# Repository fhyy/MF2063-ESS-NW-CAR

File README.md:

clear
To access the flag on your phone or computer, go to [this site.](https://fhyy.github.io/MF2063-ESS-NW-CAR/index.html)  
If you have an Android phone, you could instead install the program from the [MF2063-ESS-NW-CAR-AndroidApp](https://github.com/fhyy/MF2063-ESS-NW-CAR-AndroidApp) repository.

# Introduction
**Network diagram**  

# Instructions
_TODO_

# Contributing

## Coding conventions

The project follows a set of coding guidelines to keep the code consistent between the files. The guidelines have been adopted from the Mono project and can be found [here](https://github.com/mono/website/blob/gh-pages/community/contributing/coding-guidelines.md) ([alternative link](https://www.mono-project.com/community/contributing/coding-guidelines/)). Note that thesse guidelines have been developed for C# and some adaption may need to happen to fit the different langauges we use. Summaries of the most important parts follow below as well as a cheat sheet.

### Indentation

Use tabs for indentation. Set your text-editor to show them as 8 spaces to incentivise little nesting of loops.

### Where to put braces

| Statement                   | Brace position |
|-----------------------------|----------------|
| Namespace                   | same line      |
| Type                        | same line      |
| Method (including ctor)     | **new line**       |
| Properties                  | same line      |
| Control blocks (if, for...) | same line      |
| Anonymous types and methods | same line      |

### File headers

File headers should inlude file name and a short description of the file as well as the authors of the files. Feel free to use the following template.

```
//
// control.c: Contains the control system functionality.
//
// Authors:
//      John Doe (johndoe@address.com)
//
// License:
//      AFL 3.0 
//
```

### Important sections/cheat sheet

- [Indentation](https://www.mono-project.com/community/contributing/coding-guidelines/#indentation)
- [Where to put spaces](https://www.mono-project.com/community/contributing/coding-guidelines/#where-to-put-spaces)
- [Where to put braces](https://www.mono-project.com/community/contributing/coding-guidelines/#where-to-put-braces)
- [Multiline parameter](https://www.mono-project.com/community/contributing/coding-guidelines/#multiline-parameters)
- [Whitespace for clarity](https://www.mono-project.com/community/contributing/coding-guidelines/#use-whitespace-for-clarity)
- [Multiline comments](https://www.mono-project.com/community/contributing/coding-guidelines/#multiline-comments)
- [Casing](https://www.mono-project.com/community/contributing/coding-guidelines/#casing)

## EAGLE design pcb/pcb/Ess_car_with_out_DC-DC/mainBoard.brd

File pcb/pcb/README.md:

# PCBs

# Board for Arduino IR esc
This is the file for the Arduino board to connect the the Speed sensor and ESC to steer them from Arduino 

# Board for Arduino ultras servo 
This is the file for the Arduino board to connect Ultrasound and steering servo.

# Ess car 
Is the file for the power unit and includes the boost converter 

# Ess car with out DC-DC
This the design for the power unit with out the boost converter.

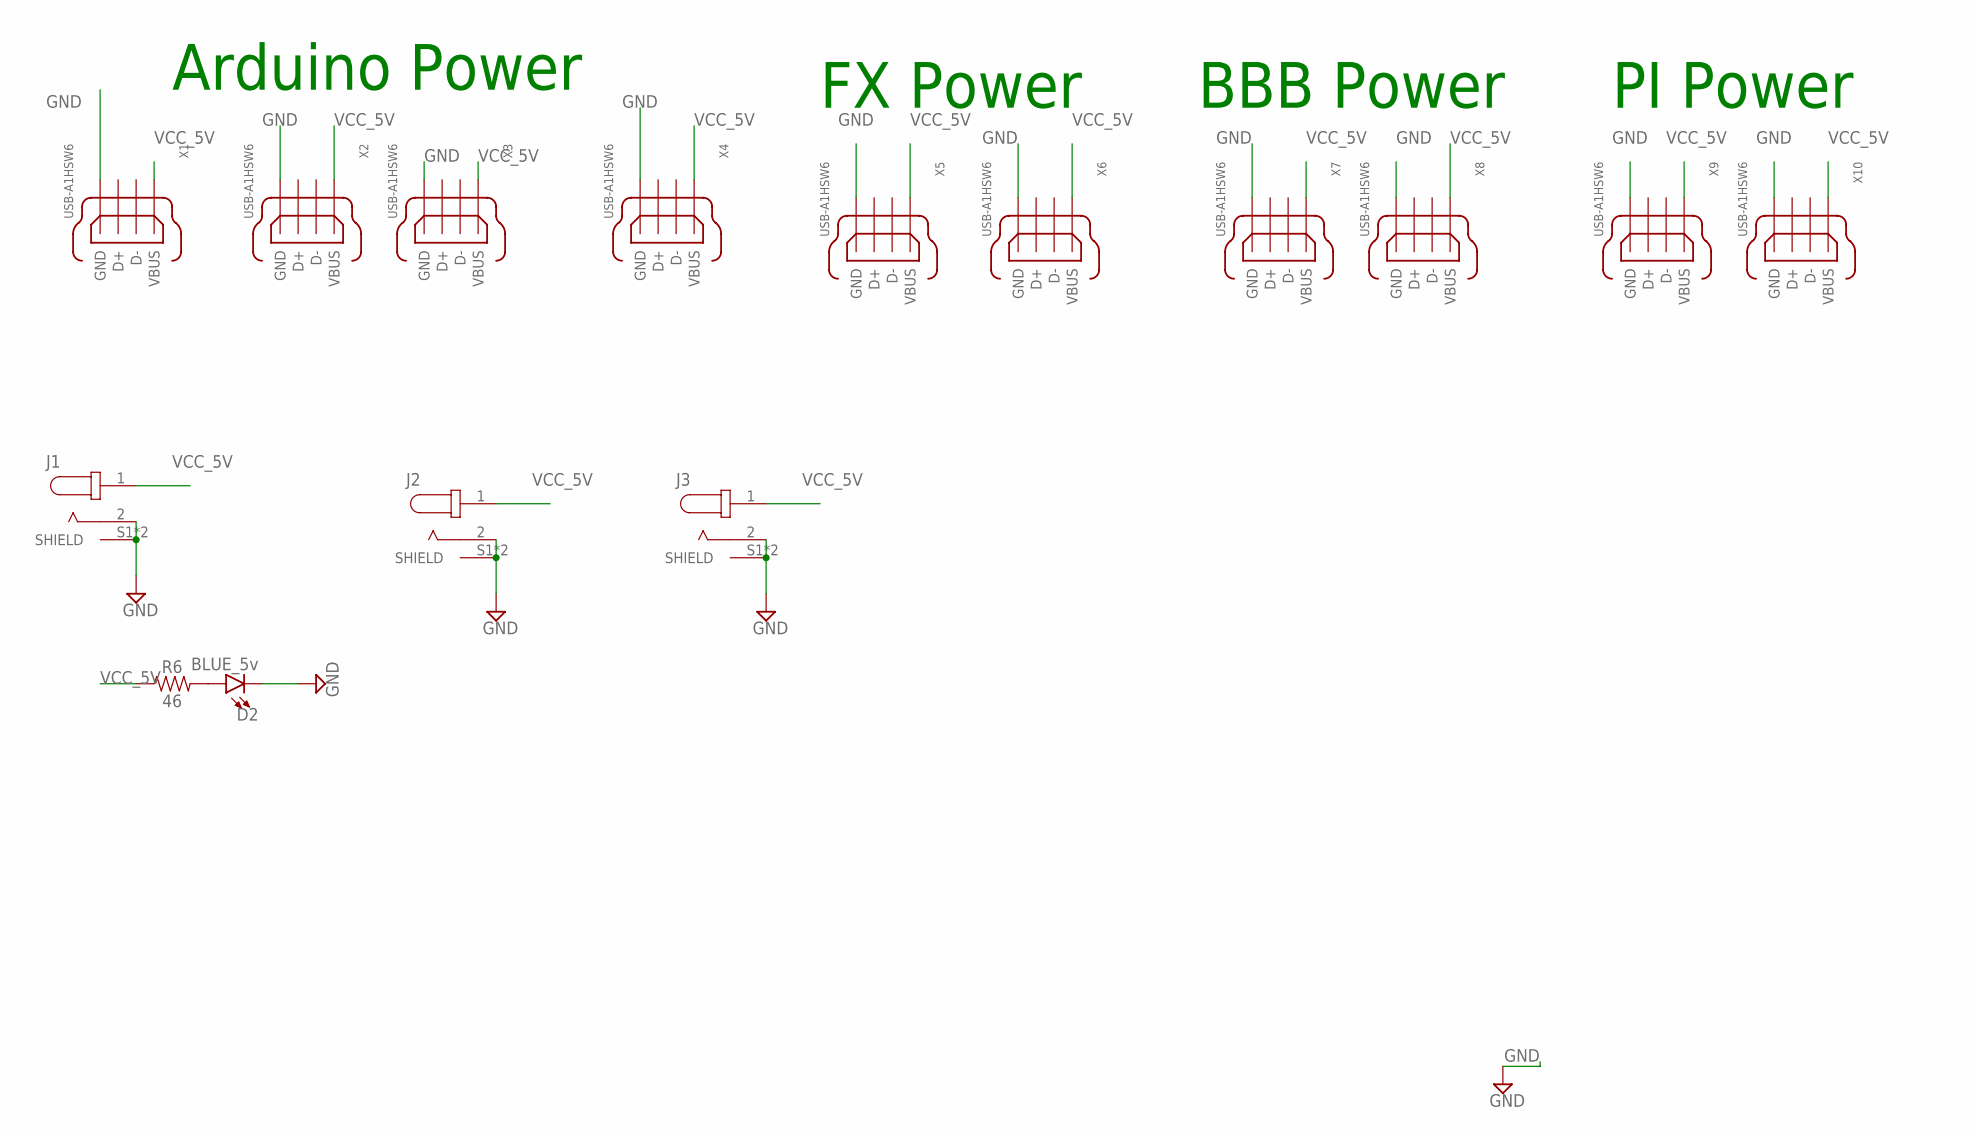
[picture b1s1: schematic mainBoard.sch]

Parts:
D2: BLUE_5v; LED-0603
J1, J2, J3: PJ-063AH; CUI_PJ-063AH
R6: 46; 0603
X1, X2, X3, X4, X5, X6, X7, X8, X9, X10: USB-A1HSW6; OST_USB-A1HSW6

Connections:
GND: D2.C, J1.2, J1.S1 (SHIELD), J1.S2 (SHIELD), J2.2, J2.S1 (SHIELD), J2.S2 (SHIELD), J3.2, J3.S1 (SHIELD), J3.S2 (SHIELD), X1.4 (GND), X2.4 (GND), X3.4 (GND), X4.4 (GND), X5.4 (GND), X6.4 (GND), X7.4 (GND), X8.4 (GND), X9.4 (GND), X10.4 (GND)
unnamed: D2.A, R6.2
VCC_5V: J1.1, J2.1, J3.1, R6.1, X1.1 (VBUS), X2.1 (VBUS), X3.1 (VBUS), X4.1 (VBUS), X5.1 (VBUS), X6.1 (VBUS), X7.1 (VBUS), X8.1 (VBUS), X9.1 (VBUS), X10.1 (VBUS)

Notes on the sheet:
Arduino Power
FX Power
BBB Power
PI Power

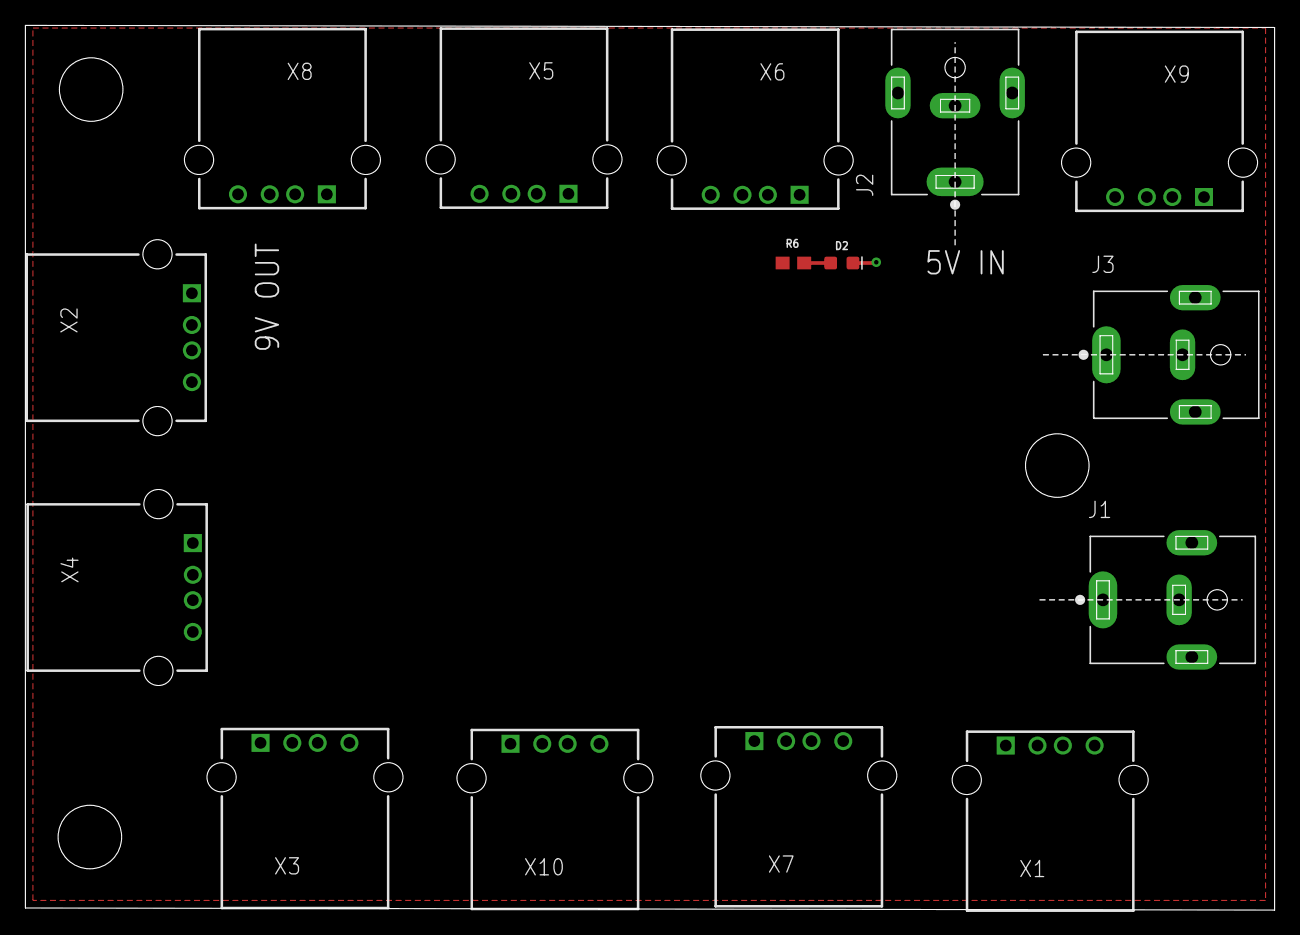
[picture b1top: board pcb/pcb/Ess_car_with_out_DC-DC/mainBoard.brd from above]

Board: 2 copper layers, 98.4 x 69.7 mm, 15 parts (0 on the bottom side), 3 nets.

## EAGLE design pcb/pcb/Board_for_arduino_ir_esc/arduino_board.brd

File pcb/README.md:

# PCB and schematics for the powering and communication 
In the "Power schematics" is the simulation file for the boost converter. The simulation program is MPLAB from Microchip and is used because the an IC from Microchip. In the folder pcb is the Eagle files for the power unit and the Arduino boards.

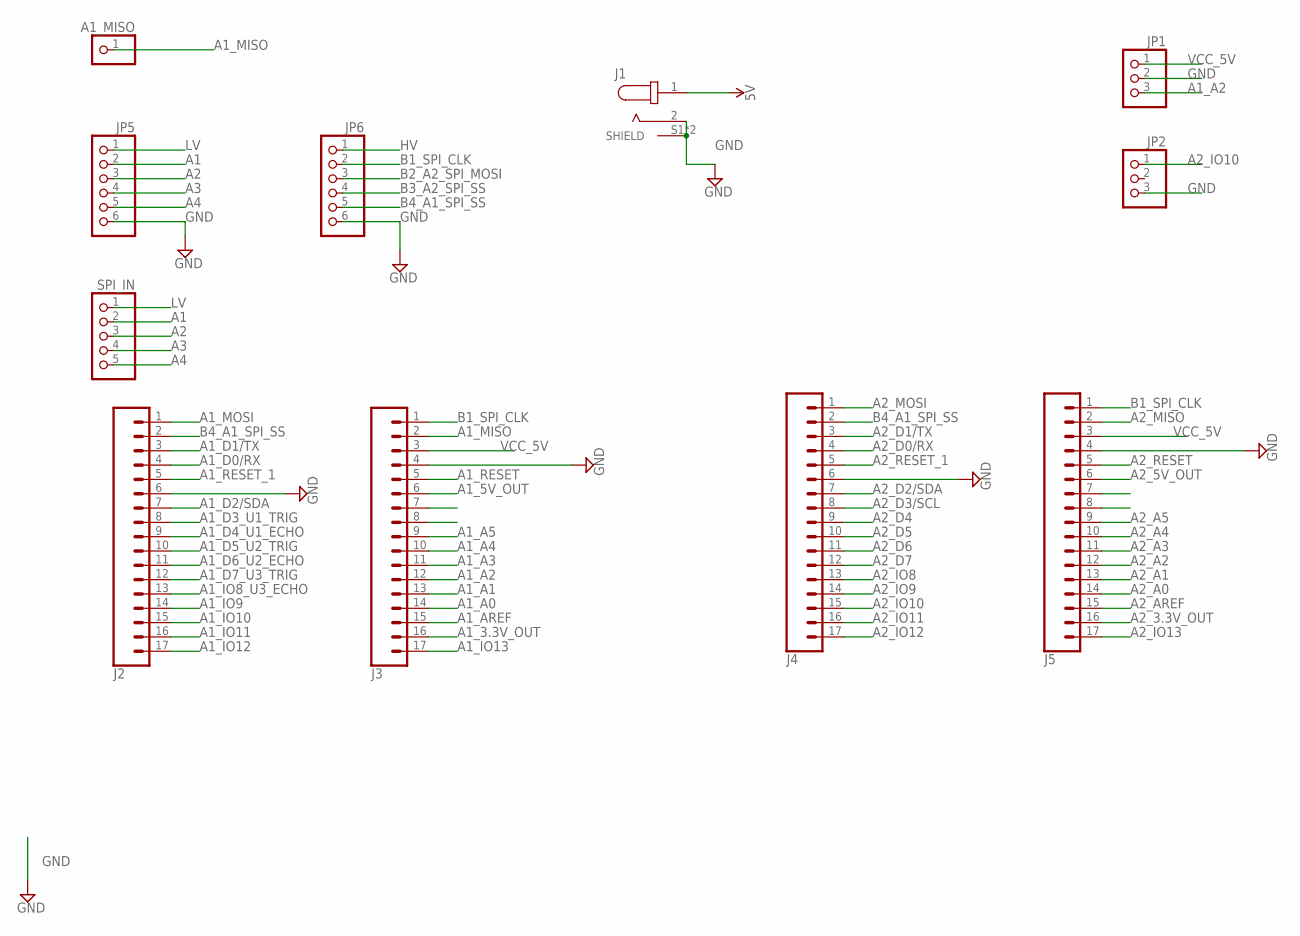
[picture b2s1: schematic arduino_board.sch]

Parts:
A1_MISO: PINHD-1X1; 1X01
J1: PJ-063AH; CUI_PJ-063AH
J2, J3, J4, J5: CONN_17; 1X17
JP1, JP2: PINHD-1X3; 1X03
JP5, JP6: PINHD-1X6; 1X06
SPI_IN: PINHD-1X5; 1X05

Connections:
5V: J1.1
A1: JP5.2, SPI_IN.2
A1_3.3V_OUT: J3.16
A1_5V_OUT: J3.6
A1_A0: J3.14
A1_A1: J3.13
A1_A2: J3.12, JP1.3
A1_A3: J3.11
A1_A4: J3.10
A1_A5: J3.9
A1_AREF: J3.15
A1_D0/RX: J2.4
A1_D1/TX: J2.3
A1_D2/SDA: J2.7
A1_D3_U1_TRIG: J2.8
A1_D4_U1_ECHO: J2.9
A1_D5_U2_TRIG: J2.10
A1_D6_U2_ECHO: J2.11
A1_D7_U3_TRIG: J2.12
A1_IO8_U3_ECHO: J2.13
A1_IO9: J2.14
A1_IO10: J2.15
A1_IO11: J2.16
A1_IO12: J2.17
A1_IO13: J3.17
A1_MISO: A1_MISO.1, J3.2
A1_MOSI: J2.1
A1_RESET: J3.5
A1_RESET_1: J2.5
A2: JP5.3, SPI_IN.3
A2_3.3V_OUT: J5.16
A2_5V_OUT: J5.6
A2_A0: J5.14
A2_A1: J5.13
A2_A2: J5.12
A2_A3: J5.11
A2_A4: J5.10
A2_A5: J5.9
A2_AREF: J5.15
A2_D0/RX: J4.4
A2_D1/TX: J4.3
A2_D2/SDA: J4.7
A2_D3/SCL: J4.8
A2_D4: J4.9
A2_D5: J4.10
A2_D6: J4.11
A2_D7: J4.12
A2_IO8: J4.13
A2_IO9: J4.14
A2_IO10: J4.15, JP2.1
A2_IO11: J4.16
A2_IO12: J4.17
A2_IO13: J5.17
A2_MISO: J5.2
A2_MOSI: J4.1
A2_RESET: J5.5
A2_RESET_1: J4.5
A3: JP5.4, SPI_IN.4
A4: JP5.5, SPI_IN.5
B1_SPI_CLK: J3.1, J5.1, JP6.2
B2_A2_SPI_MOSI: JP6.3
B3_A2_SPI_SS: JP6.4
B4_A1_SPI_SS: J2.2, J4.2, JP6.5
GND: J1.2, J1.S1 (SHIELD), J1.S2 (SHIELD), J2.6, J3.4, J4.6, J5.4, JP1.2, JP2.3, JP5.6, JP6.6
HV: JP6.1
LV: JP5.1, SPI_IN.1
VCC_5V: J3.3, J5.3, JP1.1

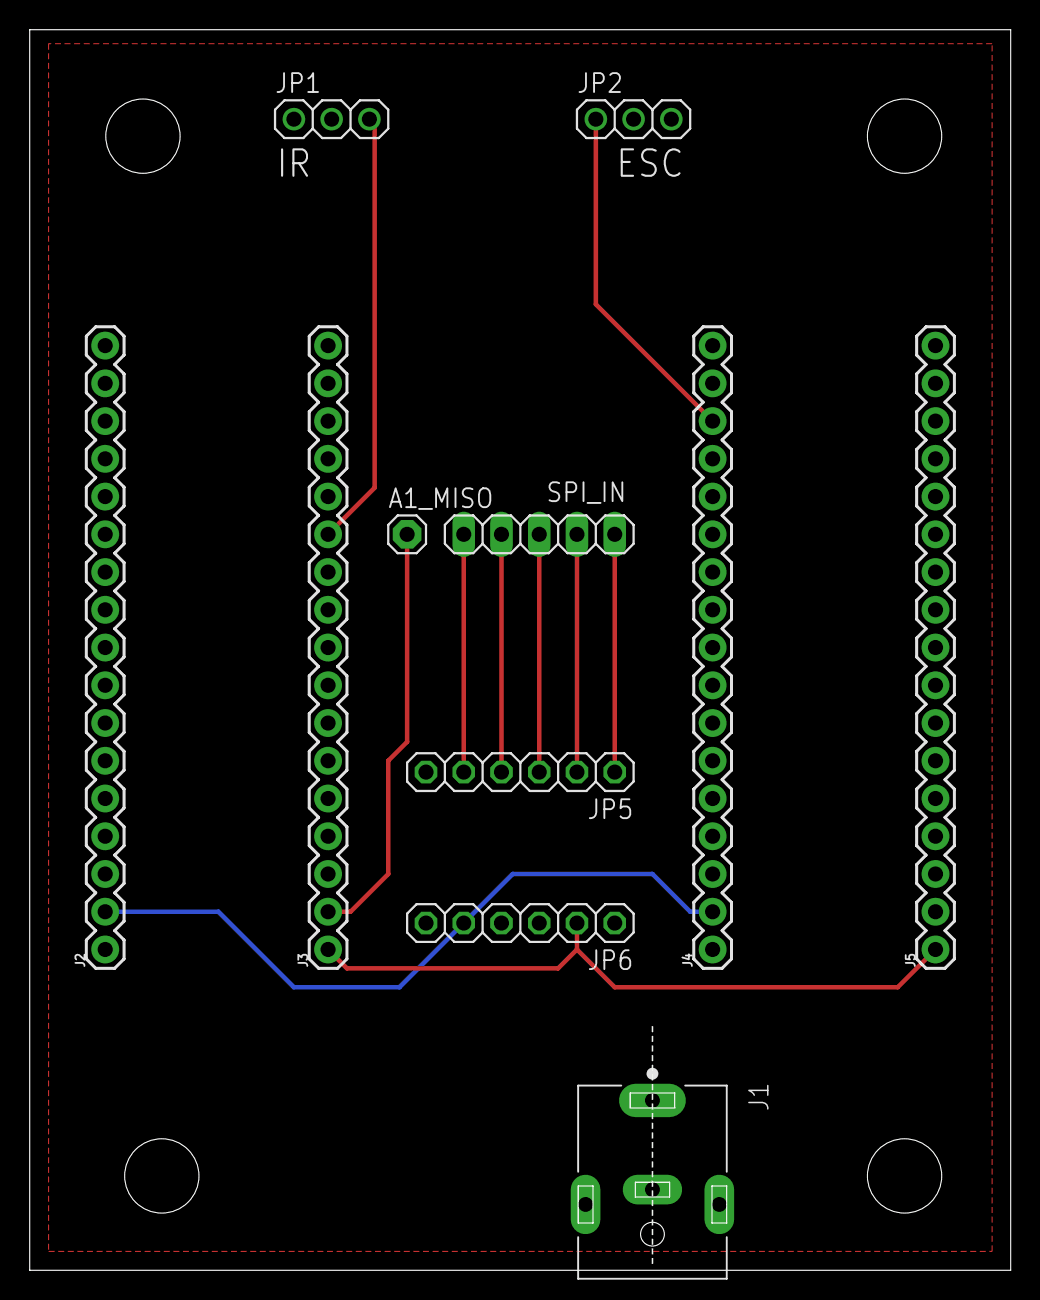
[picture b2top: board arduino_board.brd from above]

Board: 2 copper layers, 66.0 x 83.5 mm, 11 parts (0 on the bottom side), 12 nets.

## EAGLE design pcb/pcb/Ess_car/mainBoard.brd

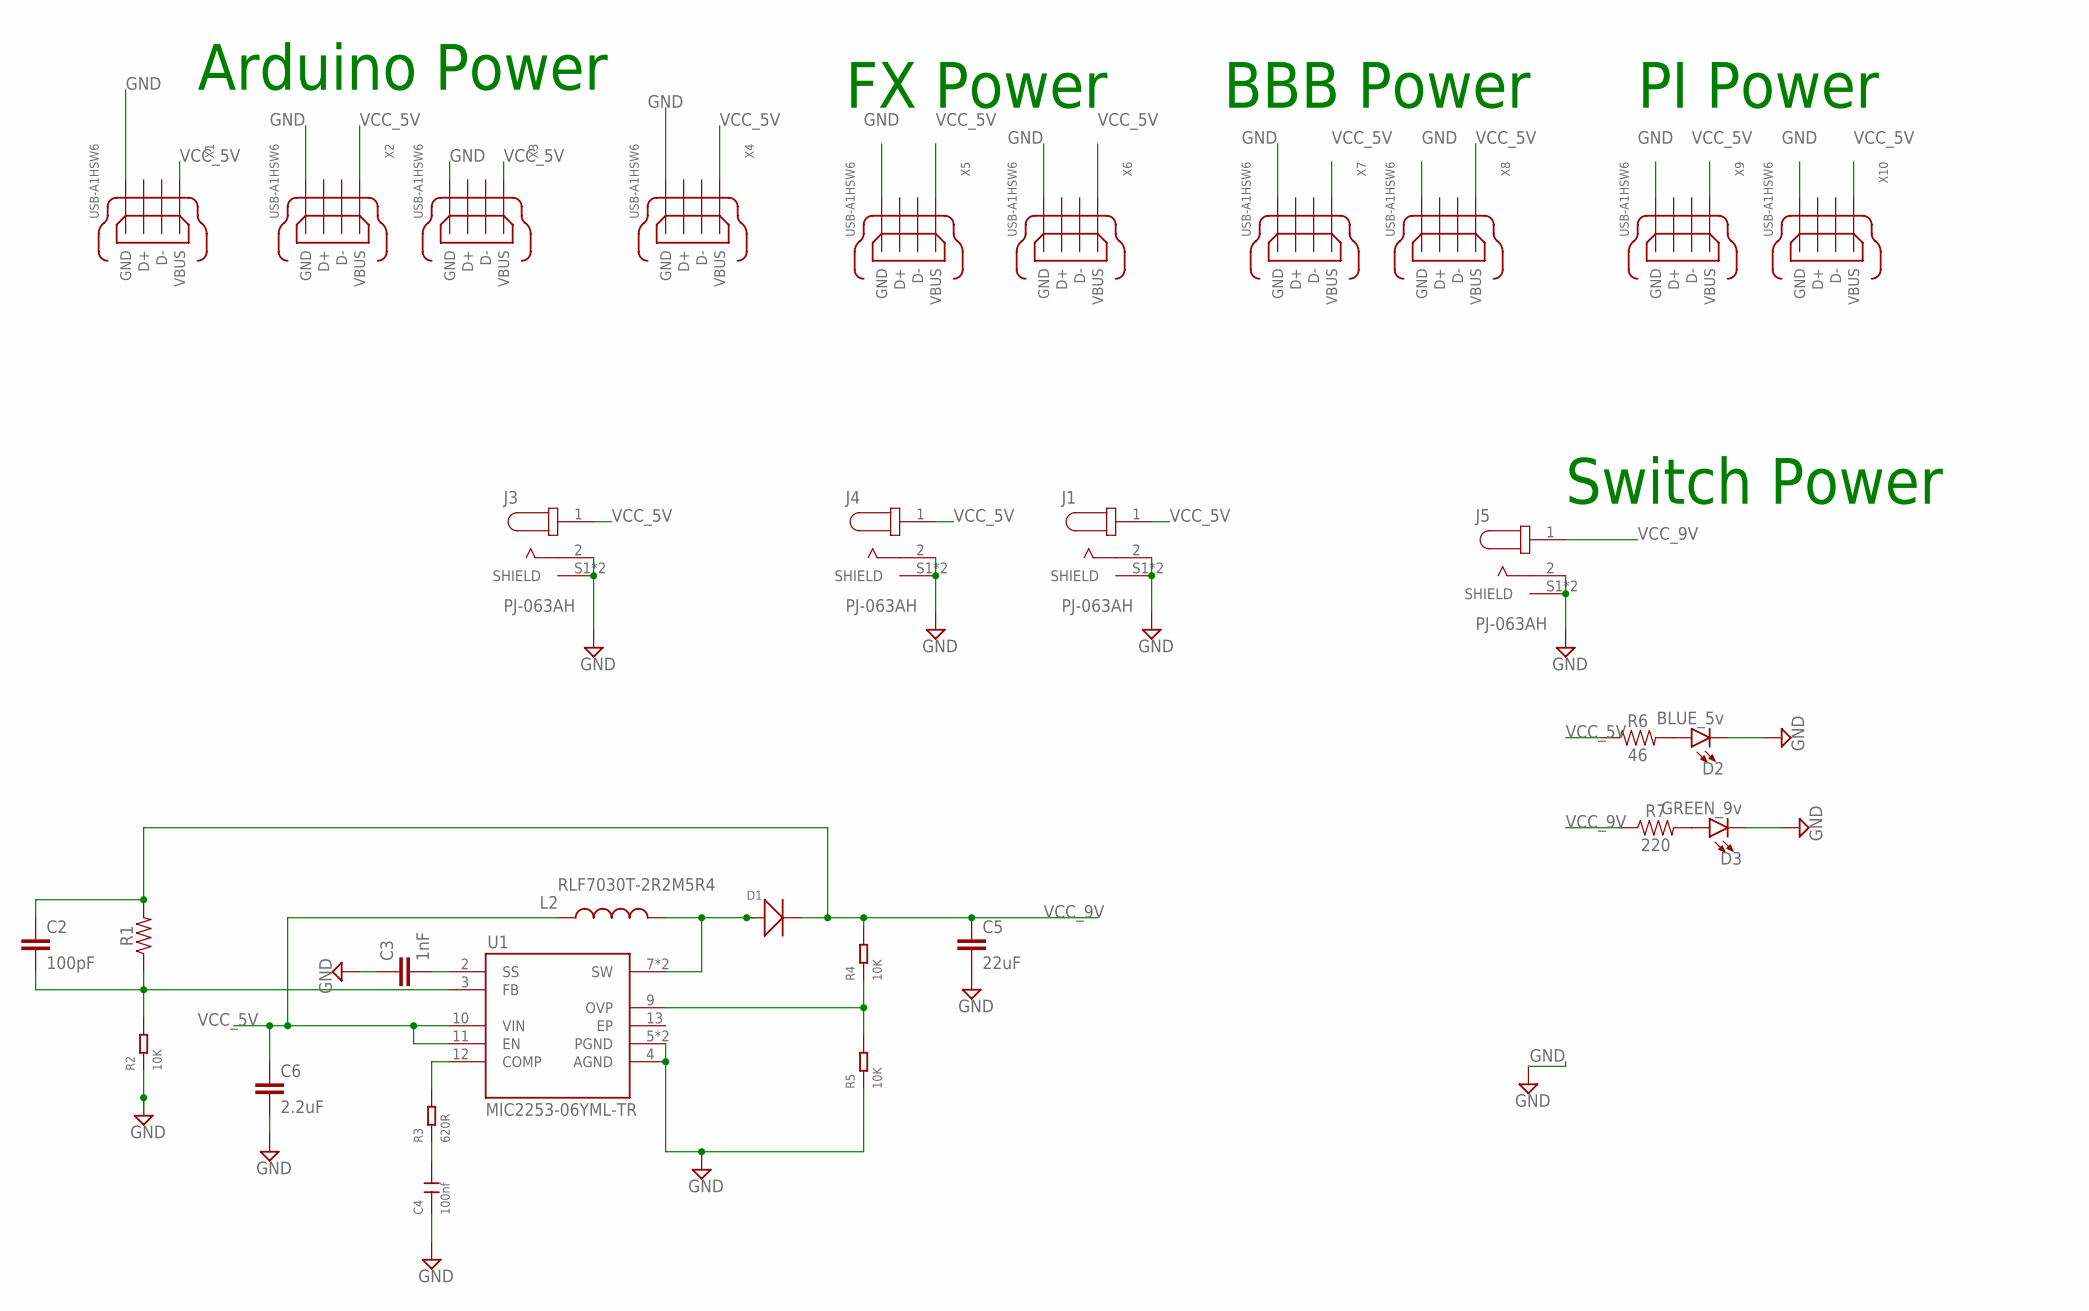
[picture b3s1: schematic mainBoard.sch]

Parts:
C2: 100pF; 0603
C3: 1nF; 0603
C4: 100nf; C0402
C5: 22uF; 0805
C6: 2.2uF; 0603
D1: SMD-DIODE-SCHOTTKY-28V-5A(DO-214AA); DO-214AA
D2: BLUE_5v; LED-0603
D3: GREEN_9v; LED-0603
J1, J3, J4, J5: PJ-063AH; CUI_PJ-063AH
L2: RLF7030T-2R2M5R4; INDP7368X320
R1: 62KOHM-0603-1/10W-5%; 0603
R2, R4, R5: 10K; R0603
R3: 620R; R0603
R6: 46; 0603
R7: 220; 0603
U1: MIC2253-06YML-TR; SON50P300X300X90-13N
X1, X2, X3, X4, X5, X6, X7, X8, X9, X10: USB-A1HSW6; OST_USB-A1HSW6

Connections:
GND: C3.1, C4.1, C5.2, C6.2, D2.C, D3.C, J1.2, J1.S1 (SHIELD), J1.S2 (SHIELD), J3.2, J3.S1 (SHIELD), J3.S2 (SHIELD), J4.2, J4.S1 (SHIELD), J4.S2 (SHIELD), J5.2, J5.S1 (SHIELD), J5.S2 (SHIELD), R2.1, R5.1, U1.4 (AGND), U1.5 (PGND), U1.6 (PGND), X1.4 (GND), X2.4 (GND), X3.4 (GND), X4.4 (GND), X5.4 (GND), X6.4 (GND), X7.4 (GND), X8.4 (GND), X9.4 (GND), X10.4 (GND)
unnamed: C3.2, U1.2 (SS)
unnamed: D2.A, R6.2
unnamed: R3.2, U1.12 (COMP)
unnamed: C4.2, R3.1
unnamed: C2.2, R1.1, R2.2, U1.3 (FB)
unnamed: R4.1, R5.2, U1.9 (OVP)
unnamed: D3.A, R7.2
unnamed: D1.+, L2.2, U1.7 (SW), U1.8 (SW)
VCC_5V: C6.1, J1.1, J3.1, J4.1, L2.1, R6.1, U1.10 (VIN), U1.11 (EN), X1.1 (VBUS), X2.1 (VBUS), X3.1 (VBUS), X4.1 (VBUS), X5.1 (VBUS), X6.1 (VBUS), X7.1 (VBUS), X8.1 (VBUS), X9.1 (VBUS), X10.1 (VBUS)
VCC_9V: C2.1, C5.1, D1.-, J5.1, R1.2, R4.2, R7.1

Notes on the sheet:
Arduino Power
FX Power
BBB Power
PI Power
Switch Power

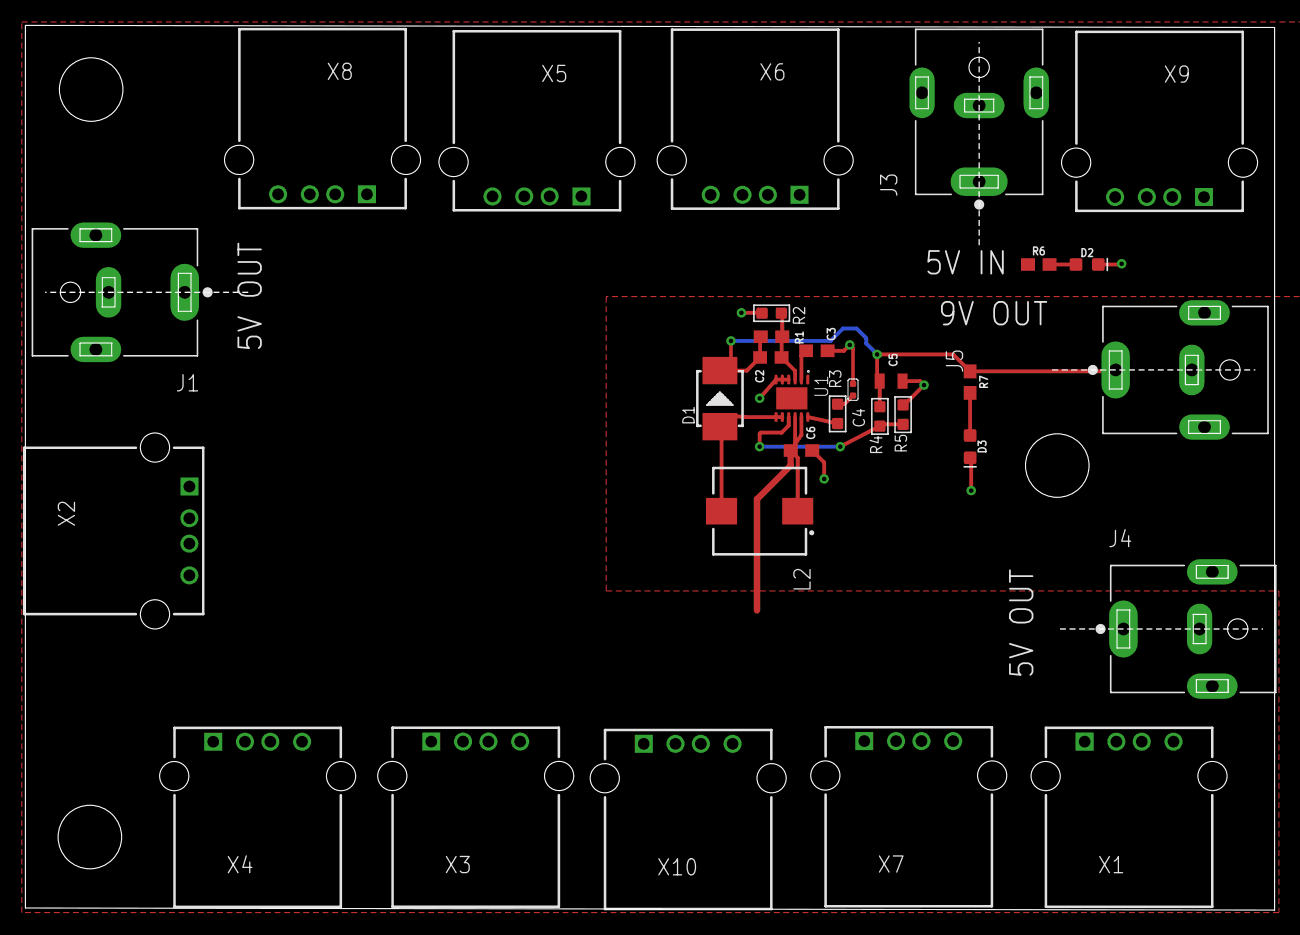
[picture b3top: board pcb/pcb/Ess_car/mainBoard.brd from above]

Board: 2 copper layers, 98.4 x 69.7 mm, 31 parts (0 on the bottom side), 11 nets.

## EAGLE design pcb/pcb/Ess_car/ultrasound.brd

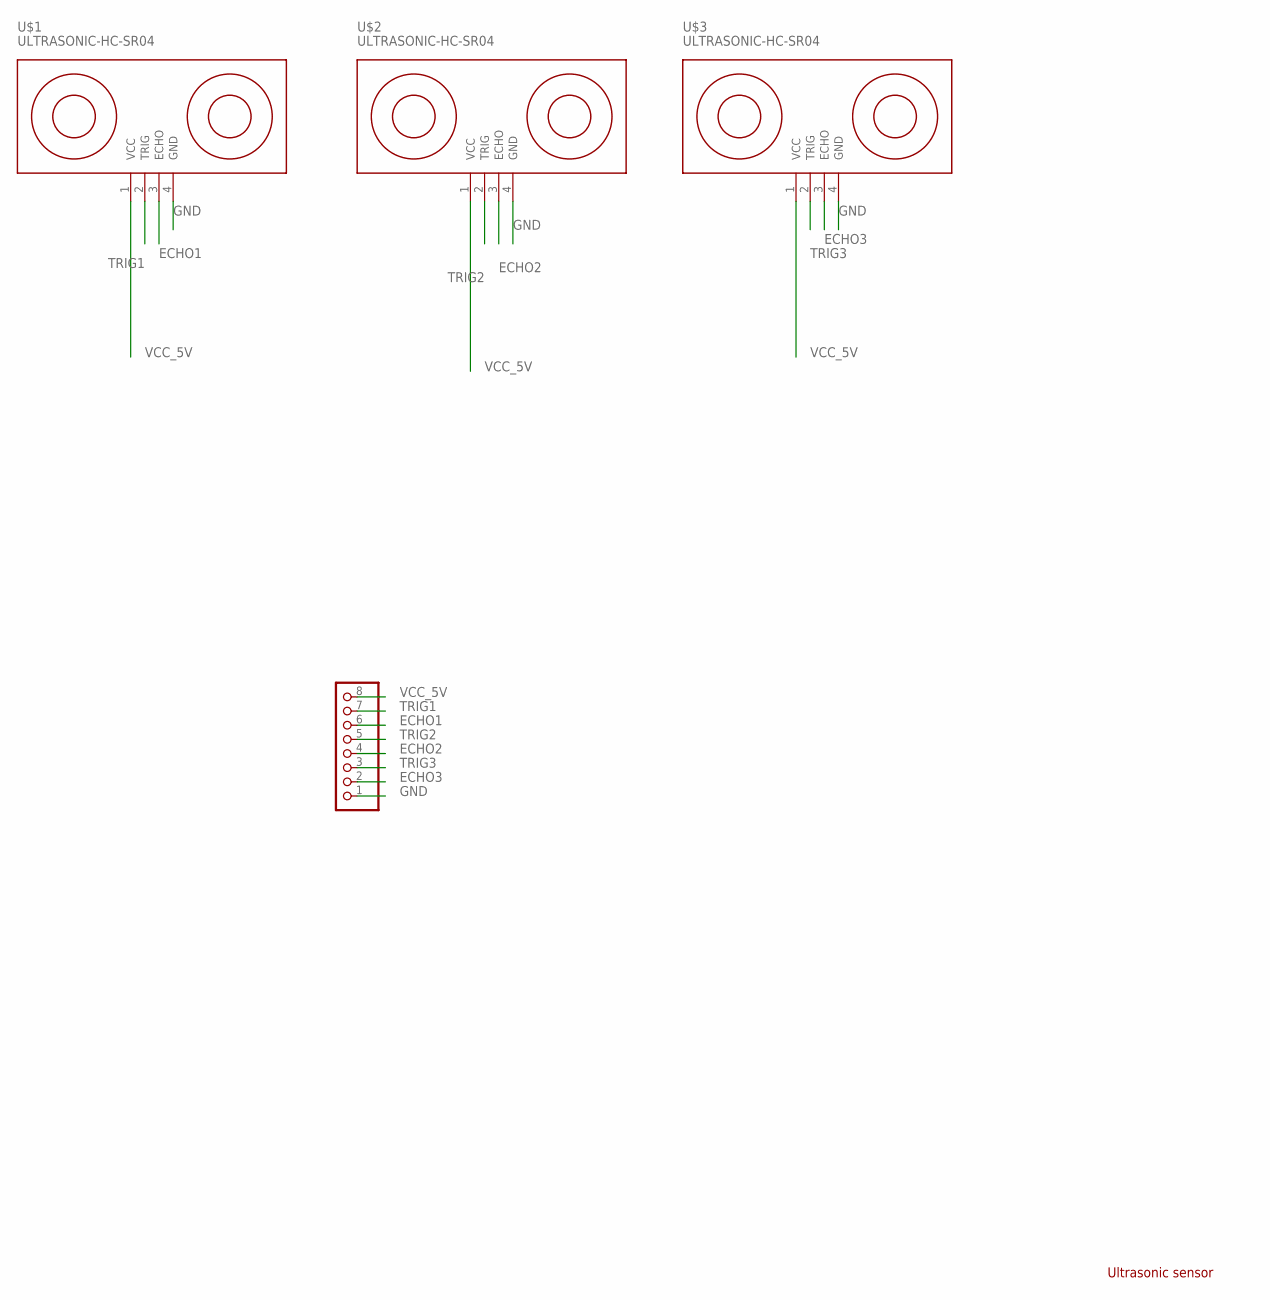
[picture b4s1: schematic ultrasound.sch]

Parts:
JP2: PINHD-1X8/90; 1X08/90
U$1, U$2, U$3: ULTRASONIC-HC-SR04

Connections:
ECHO1: JP2.6, U$1.3 (ECHO)
ECHO2: JP2.4, U$2.3 (ECHO)
ECHO3: JP2.2, U$3.3 (ECHO)
GND: JP2.1, U$1.4 (GND), U$2.4 (GND), U$3.4 (GND)
TRIG1: JP2.7, U$1.2 (TRIG)
TRIG2: JP2.5, U$2.2 (TRIG)
TRIG3: JP2.3, U$3.2 (TRIG)
VCC_5V: JP2.8, U$1.1 (VCC), U$2.1 (VCC), U$3.1 (VCC)

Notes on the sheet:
Ultrasonic sensor

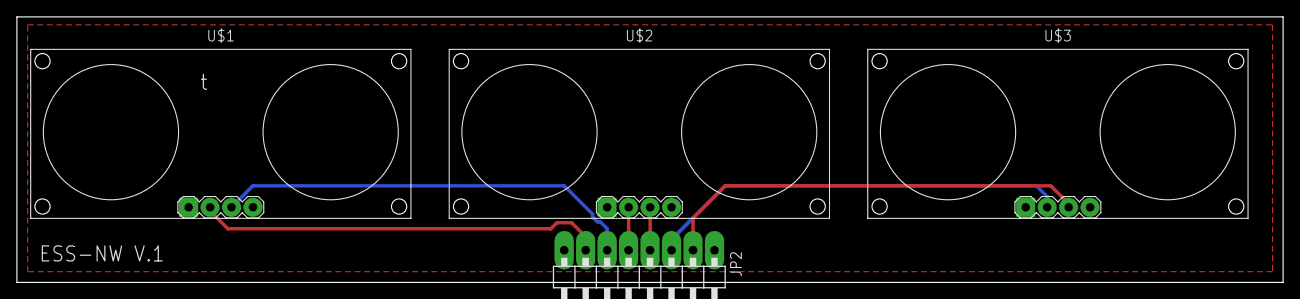
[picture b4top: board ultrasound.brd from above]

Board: 2 copper layers, 149.8 x 31.4 mm, 4 parts (0 on the bottom side), 8 nets.

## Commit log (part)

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2018-11-21 Added comments and @author field for doxygen
2018-11-21 Add wrapper class for shared memory
2018-11-21 Add class for cyclic buffer
2018-11-21 Set required Boost version to 1.62 + code style
2018-11-22 Create process to handle SPI communication
2018-11-22 Add simple makefile
2018-11-22 Add library files for cyclic buffer
2018-11-22 Initial README.md update
2018-11-22 Add library files for shared memory
2018-11-22 Add script to set up BBB for SPI communication
2018-11-22 Basic services + Embreak WORKING with dummy data
2018-11-22 Controller working with dummy data and no ESSPrototype
2018-11-22 Automise entry of info into uEnv.txt
2018-11-22 Moved main to class definition, pass argument to ctr via terminal
2018-11-22 Include SharedMemory and CyclicBuffer
2018-11-23 Writes to shared buffer, getting segfaults. Restructured files.
2018-11-23 No more segfaults
2018-11-23 No notification if no sensor data was read
2018-11-23 default constructor added
2018-11-23 shared memory implemented
2018-11-23 shared memory, terminates with CSharedMemoryException
2018-11-23 compiles but throws CSharedMemoryExcepion
2018-11-24 daily commit
2018-11-24 uodate
2018-11-24 Shared memory w/ distance sensor, UNTESTED
2018-11-24 Added IDs for camera node
2018-11-24 Added camera and setmin functionality
2018-11-24 Adheres to packet specifications
2018-11-24 Added shutdown functionality to ESSPrototype
2018-11-25 Changes password of user debian
2018-11-26 Minor bugfixes, commented out part of update_go_status()
2018-11-26 update main.cpp and adapt car_controller_statemachine files
2018-11-26 use pointer insted of the object itself as input in statemachine file
2018-11-26 Add README.md for NuSMV testing
2018-11-26 Added skip-go flag for debugging, fixed ID error
2018-11-26 fixed error with types in run_di()
2018-11-27 distance.cpp replaced with dummy generator, ipc working
2018-11-27 Shared memory init restructured
2018-11-27 Minor bugfix for debug printout
2018-11-27 Update to version talking with debain9
2018-11-27 Speed+distance sensors and steer request working over vsomeip
2018-11-27 code cleaning and comments, cond comp for debug msgs
2018-11-28 General code cleaning. Added handler for SETMIN requests in MoSpServ.
2018-11-29 Misspelled folder name corrected (contoller => controller)
2018-11-29 simple script for deploying bbb-code
2018-11-29 Minor changes to debug output
2018-11-29 Test run of a bunch of library methods. Getting segfaults
2018-11-29 add shm2ard_st part (zero confidence level)
2018-11-29 Add missing case to model
2018-11-29 Finishes test suite, UNTESTED on actual network
2018-11-29 Changed SPI specification for receiving 2 bytes without risk of sync errors
2018-11-29 Minor aesthetic change to debug output
2018-11-29 IPC comm through shared mem implemented but untested
2018-11-29 add go status in statemachine
2018-11-29 arduino_di pin configure correctness
2018-11-29 IPC between essprototype program and vsomeip seems ok
2018-12-01 Status report 4, first draft
2018-12-01 Steer/Dist systems working over network
2018-12-01 use pointer as function input var
2018-12-01 Link needed libraries
2018-12-01 Fix spi working every other execution
2018-12-01 Revert to 9325b29
2018-12-01 Adhere to new folder structure
2018-12-01 Fix spi to work every execution
2018-12-01 Add debug flag
2018-12-01 Cleanup spi init script
2018-12-01 Move spi init script
2018-12-01 Spi works every time for dist-steer
2018-12-01 move controller-statemachine file into lib folder
2018-12-01 ESSPrototype now reads dist sensors correctly, no auto shutdown on embreak
2018-12-01 Clearer test stuite output, removed shutdown test
2018-12-01 untested camera implementation
2018-12-01 Revert "Fix producer and consumer startup sequence to any"
    This reverts commit 606e9844c547fa880c12aa54be5b1d35961313cd.
2018-12-01 test version1
2018-12-01 Now deploys rpi-vision code aswell
2018-12-01 Remove "blind" value of state variables
2018-12-01 Rename folder
2018-12-01 Update spi script for debian 9
2018-12-01 Renamed folder, uncommented debug msgs
2018-12-01 gitignore for c++ subprocess
2018-12-02 Created a html based page for use as red/green flag
2018-12-02 Started writing on testing protocols
2018-12-03 Update cyclic buffer for car controller
2018-12-03 Removed old TODO, fixed error in test suite
2018-12-03 change macro steering angle number definitions
2018-12-03 minor debug print changes, CMake now copies pyscript to build
2018-12-03 code update
2018-12-03 cmake build system for statemachine code
2018-12-03 bugs fixed in ctrl-sm lib
2018-12-03 Update README.md with autostart information
2018-12-03 Fix README.md formatting
2018-12-03 init of pp and poster
2018-12-03 Updated debug msgs
2018-12-03 python function
    turn the color detection code into a function, which supposed to be called by c++ code.
2018-12-04 fix string display problem
2018-12-05 Removed .DS_Store
2018-12-05 blind camera and goStatus in statemachine temporarily, used for test
2018-12-05 Got all input messages into statemachine
2018-12-05 DEBUG macro for distance.cpp, macro for wakeup notifications in c_c_c.cpp
2018-12-05 fix statemachine stuck in standstill state problem
2018-12-05 linuxpipes tested, no good results
2018-12-05 Updated network-diagram
2018-12-05 shell for interactively controlling the car, UNTESTED
2018-12-05 Cosmetic updates to shell, no debug from ESSPRototype class
2018-12-05 Added updated svg figure
2018-12-05 Setmin distance now available
2018-12-05 Get go status now implemented in shell
2018-12-05 draft of poster
2018-12-05 Update presentation
2018-12-05 Cosmetic stuff for shell banner
2018-12-05 get goStatus before other sm input
2018-12-05 remove bootup, put it in ctrl lib
2018-12-05 correct the True->evTrue bug
2018-12-05 Changed png diagram to new version
2018-12-05 fix of poster
2018-12-05 Add pictures for presentation
2018-12-05 Proposal of changes, added fun logo
2018-12-06 new frames for sdn and assembely
2018-12-06 bug fix
2018-12-06 Change spelling error in a headline
2018-12-06 Last minute changes to the presentation
2018-12-06 Camera working but slow
2018-12-06 Folder restructure to match other nodes
2018-12-06 Updated flag colors
2018-12-06 Better colors
2018-12-06 add kthLogo in title page
2018-12-06 edit page head
2018-12-06 lib only in one place, deploy script handles EVERYTHING. UNTESTED!
2018-12-07 lib folder missing simple gpio library
2018-12-07 add list of figures and tables, make overall structure better
2018-12-07 Added missing library
2018-12-07 Now adds user to group sudo. User won't have to type passwd with sudo
2018-12-07 PATH will contain debian's local bin folder
2018-12-07 add implementation section structure draft
2018-12-07 New sudoers cfg for more convenient start/stop of programs
2018-12-07 make install added to vsomeip install script
2018-12-07 save before switch to poster
2018-12-07 Updated but untested PI controller
2018-12-07 edit report header
2018-12-07 Rebase of repo to minimize unnecessary work. Mostly working deploy script
2018-12-07 change structure of implementation chapter
2018-12-07 add textcomp package, get correct micro second unit display
2018-12-07 Updated documentation
2018-12-07 Added more test cases for sensor and actuator nodes
2018-12-08 add part of distance sensor implementation
2018-12-08 chmod -x
2018-12-08 send half of target speed to motor arduino
2018-12-08 Call OpenCV using Python/C API, UNTESTED
2018-12-08 Minor fixes, still UNTESTED
2018-12-08 Build works
2018-12-08 Remove hardware SPI-init code from distance
2018-12-08 Remove hardware SPI-init code from speed
2018-12-08 Sets speed to 0 on embreak
2018-12-08 Fixed typo in variable name
2018-12-08 add camera part
2018-12-08 add shared mem subsection
2018-12-08 Updated motor controller, and added comments for how to adjust the functionality
2018-12-08 change position part
2018-12-09 No longer builds doc
2018-12-09 fix no lastpage in page head
2018-12-09 remove vscode trash file
2018-12-09 Properly copies linux_cfg onto targets
2018-12-09 SPI implementation text draft
2018-12-09 calls vsomeip services with sudo
2018-12-09 add literature spi subsection draft
2018-12-09 No function, only a while-loop
2018-12-09 add float package, update spi connection figure
2018-12-09 Update report
2018-12-09 add fun logo in title page
2018-12-09 Aesthetic change to shell, minor checkDistance bugfix on ccc
2018-12-09 Add SPI settings that dont survive
2018-12-09 remove redundant clearpage
2018-12-10 change speed macro setup
2018-12-10 change sleep time to 180ms
2018-12-10 Add robots to final slide
2018-12-10 object detection with Neural Network
2018-12-11 add report disposition
2018-12-11 put network under literature section
2018-12-11 Update report with reflective object sensor
2018-12-11 Added and formatted documentation for use with doxygen
2018-12-11 Add state machine verfication to report
2018-12-11 Fixed one test case and deleted already tested cases
2018-12-11 Add project management to report
2018-12-11 code for sdn
2018-12-11 pcb,power simulations
2018-12-11 power schametic
2018-12-11 Removed additional servo writes
2018-12-11 Stops car when services are missing
2018-12-11 Different name for executable
2018-12-11 Minor code style fix
2018-12-11 Added part about ESC and Servo
2018-12-11 Minor compilation error fix
2018-12-11 Move section of text regarding testing in report
2018-12-11 Fix merge
2018-12-11 project description added
2018-12-11 Fix conflicts
2018-12-11 Remove old conflict
2018-12-11 vision details
2018-12-11 Added text that had gone missing
2018-12-11 update README and code comment in ard_di
2018-12-11 git pull
2018-12-11 future work
2018-12-11 spell check
2018-12-11 system overview added
2018-12-11 add some text in distance sensor
2018-12-11 First draft of Software Architecture
2018-12-11 modification
2018-12-11 new thing in fuater work
2018-12-11 Add acronyms to report
2018-12-11 First iteration of the abstract in the report
2018-12-11 Added testing and verification text and appendix
2018-12-11 More text to background
2018-12-11 Add text about risk analysis in report
2018-12-11 cosmetic code changes
2018-12-11 spel check
2018-12-11 karlquist reference added
2018-12-11 Fixed all ?? errors in pdf
2018-12-11 discussion about sw arch
2018-12-11 fig fix
2018-12-11 Abstract, first draft
2018-12-11 new figuers
2018-12-11 Add results to the report
2018-12-11 Final report, as handed in onon canvas
2018-12-12 Add template of management report
2018-12-12 Final version, added a bunch of \centering
2018-12-12 Updated READMES, added make install to script
2018-12-12 Removed old READMEs
2018-12-12 Update title page of report
2018-12-12 Added some lines about deploy_code.sh and cfg_bbb
2018-12-12 Added lines about script and about folder object_detection
2018-12-12 Added lines about script and about folder object_detection 2
2018-12-12 Started figures folder
2018-12-12 Updated filenames in figure
2018-12-12 readme
2018-12-12 Added comments
2018-12-12 attempt to fix table
2018-12-12 Fixed tables
2018-12-12 clean ard-speed folder
2018-12-12 removed unused folders
2018-12-12 Add file for doxygen
2018-12-12 add comment for doxygen
2018-12-12 edit ard-distance folder structure
2018-12-12 fix README table
2018-12-12 edit comment
2018-12-13 Doxygen comments for all members
2018-12-13 Fixed some minor Doxygen warnings
2018-12-13 Some Doxygen comments added
2018-12-13 documentation on RPI vision
2018-12-13 Ignores lib-folder in node-specific folder
2018-12-13 Corrected declaration that had been messed up during commenting
2018-12-13 Fixed bad grammar
2018-12-13 documentation
2018-12-13 Added test results to test cases
2018-12-13 add latest EVM figure
2018-12-13 Goals-section finished
2018-12-13 No longer ignores pdfs-for status reports and final management report
2018-12-13 Figures added
2018-12-14 Update README.md with SPI information
2018-12-14 fix table display
2018-12-14 Section 3 begun
2018-12-14 Section 3 begun, compiles
2018-12-14 General summary, draft 1
2018-12-14 Removed references section
2018-12-14 Final report, as handed in on Canvas

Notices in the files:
parts and their libraries:
SparkFun-Connectors: Licensing: Creative Commons ShareAlike 4.0 International - https://creativecommons.org/licenses/by-sa/4.0
diy-modules: Released under the Creative Commons Attribution 4.0 International License: http://creativecommons.org/licenses/by/4.0
